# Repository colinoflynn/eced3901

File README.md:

ECED3901 - The Git REPO
-------------------------------
This GIT repo contains a lot of raw material from me teaching ECED3901 at Dalhousie University.
Be warned it's not designed to be used directly, but is provided as a service to those who might
need something from my teaching (source files, example code, etc.).

If you are taking the course, please consider the material on BBLearn (at dal.ca/bblearn) to be the
definitive resource. Things on this git repo are often *incomplete* or possibly even wrong for your
class.

Everything inside this repo can be assumed to be licensed CC-BY where possible (i.e. there is no more
restrictive license placed on it).

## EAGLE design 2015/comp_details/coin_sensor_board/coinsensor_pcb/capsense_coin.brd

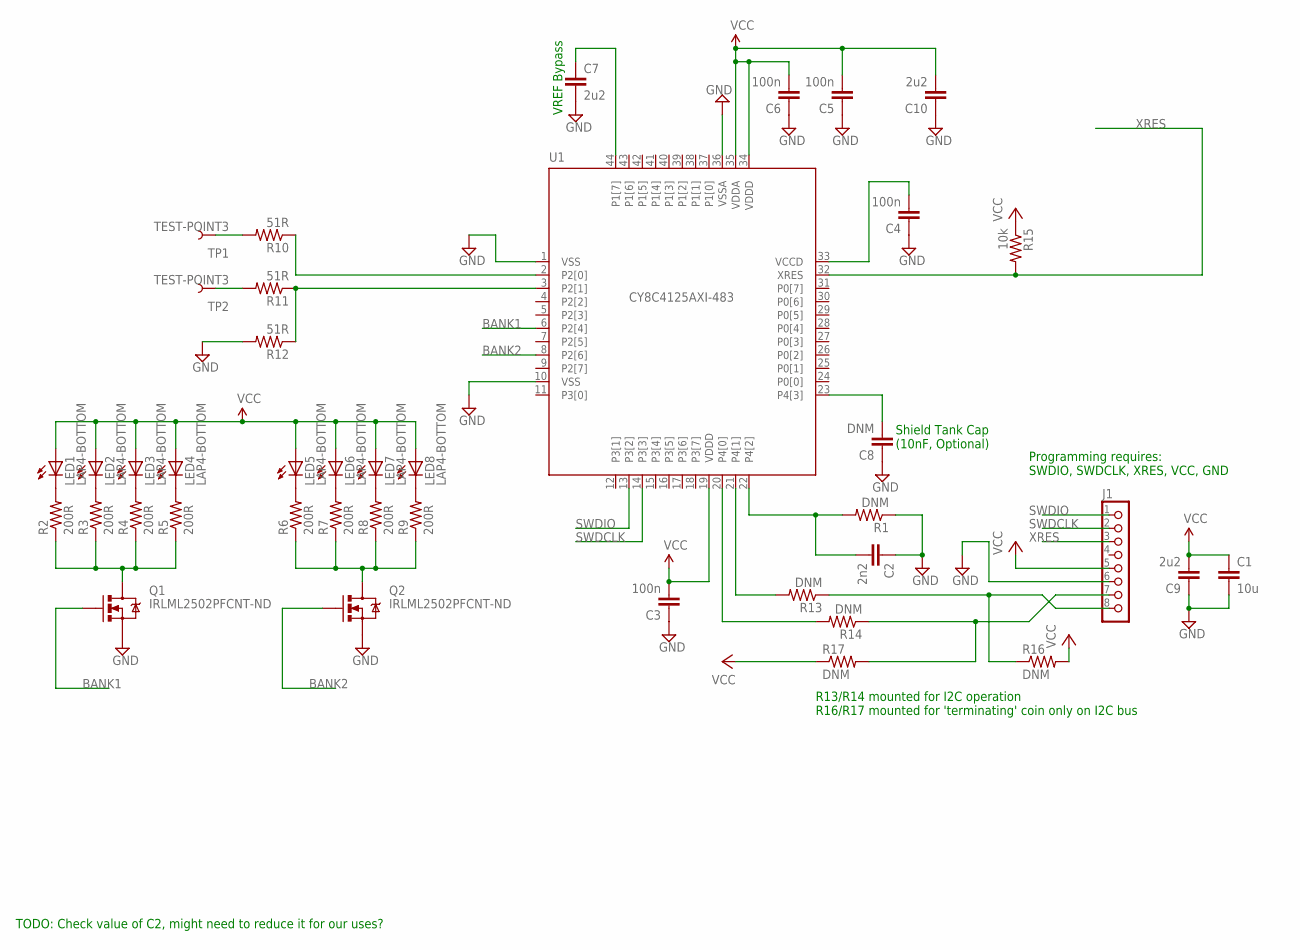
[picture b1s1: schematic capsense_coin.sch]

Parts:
C1: 10u; 0603C
C2: 2n2; 0603C
C3, C4, C5, C6: 100n; 0603C
C7, C9, C10: 2u2; 0603C
C8: DNM; 0603C
J1: CON_HEADER_1X08; DF13C-VERTSMD
LED1, LED2, LED3, LED4, LED5, LED6, LED7, LED8: LAP4-BOTTOM; P47F-BOTTOM
Q1, Q2: IRLML2502PFCNT-ND; SOT23
R1, R13, R14, R16, R17: DNM; 0603R
R2, R3, R4, R5, R6, R7, R8, R9: 200R; 0603R
R10, R11, R12: 51R; 0603R
R15: 10k; 0603R
TP1, TP2: TEST-POINT3; PAD.03X.03
U1: CY8C4125AXI-483; TQFP44

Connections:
BANK1: Q1.1 (G), U1.6 (P2[4])
BANK2: Q2.1 (G), U1.8 (P2[6])
GND: C1.2, C2.1, C3.1, C4.1, C5.1, C6.1, C7.2, C8.1, C9.1, C10.1, J1.6, Q1.2 (S), Q2.2 (S), R1.1, R12.2, U1.1 (VSS), U1.10 (VSS), U1.36 (VSSA)
unnamed: C2.2, R1.2, U1.22 (P4[2])
unnamed: C7.1, U1.44 (P1[7])
unnamed: C4.2, U1.33 (VCCD)
unnamed: C8.2, U1.23 (P4[3])
unnamed: LED1.C, R2.2
unnamed: LED2.C, R3.2
unnamed: LED3.C, R4.2
unnamed: LED4.C, R5.2
unnamed: LED5.C, R6.2
unnamed: LED6.C, R7.2
unnamed: LED7.C, R8.2
unnamed: LED8.C, R9.2
unnamed: Q1.3 (D), R2.1, R3.1, R4.1, R5.1
unnamed: Q2.3 (D), R6.1, R7.1, R8.1, R9.1
unnamed: R10.1, U1.2 (P2[0])
unnamed: R11.1, R12.1, U1.3 (P2[1])
unnamed: R13.2, U1.21 (P4[1])
unnamed: R14.2, U1.20 (P4[0])
unnamed: J1.8, R13.1, R16.1
unnamed: J1.7, R14.1, R17.2
P0[6]: U1.30 (P0[6])
P1[2]: U1.39 (P1[2])
P2[2]: U1.4 (P2[2])
P3[6]: U1.17 (P3[6])
SENSE: R10.2, TP1.P$1
SHIELD: R11.2, TP2.P$1
SWDCLK: J1.2, U1.14 (P3[3])
SWDIO: J1.1, U1.13 (P3[2])
VCC: C1.1, C3.2, C5.2, C6.2, C9.2, C10.2, J1.5, LED1.A, LED2.A, LED3.A, LED4.A, LED5.A, LED6.A, LED7.A, LED8.A, R15.1, R16.2, R17.1, U1.19 (VDDD), U1.34 (VDDD), U1.35 (VDDA)
XRES: J1.3, R15.2, U1.32 (XRES)

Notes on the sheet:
Shield Tank Cap (10nF, Optional)
VREF Bypass
R13/R14 mounted for I2C operation R16/R17 mounted for 'terminating' coin only on I2C bus
Programming requires: SWDIO, SWDCLK, XRES, VCC, GND
TODO: Check value of C2, might need to reduce it for our uses?

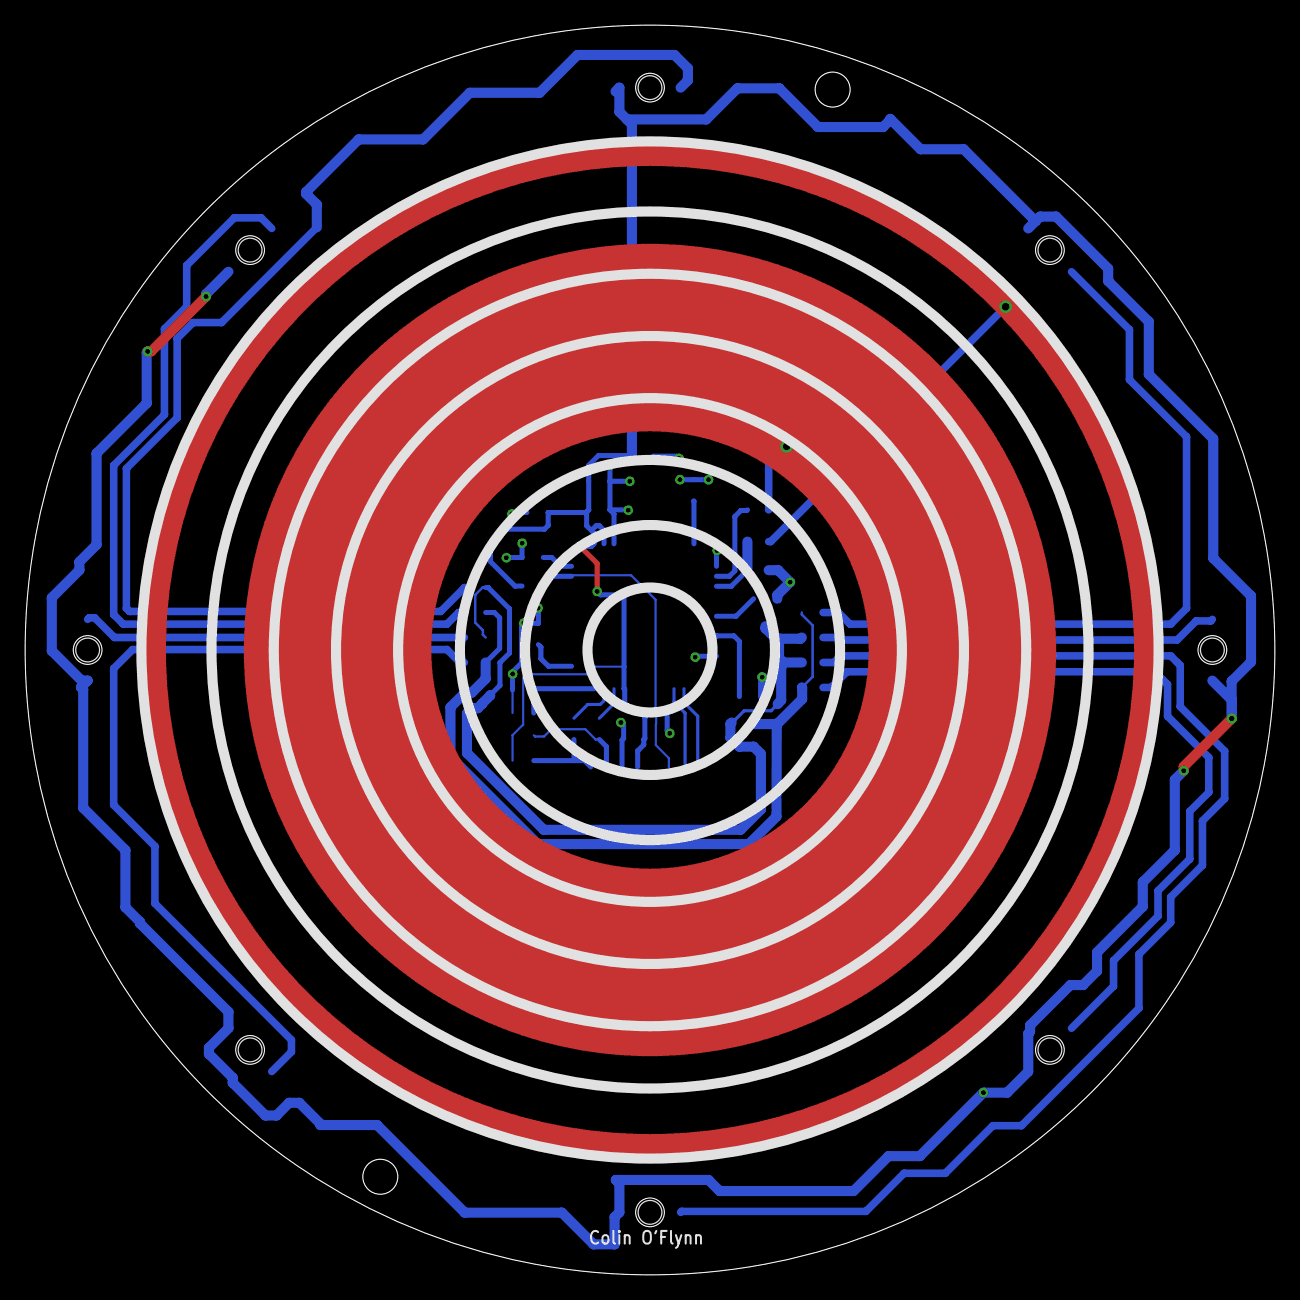
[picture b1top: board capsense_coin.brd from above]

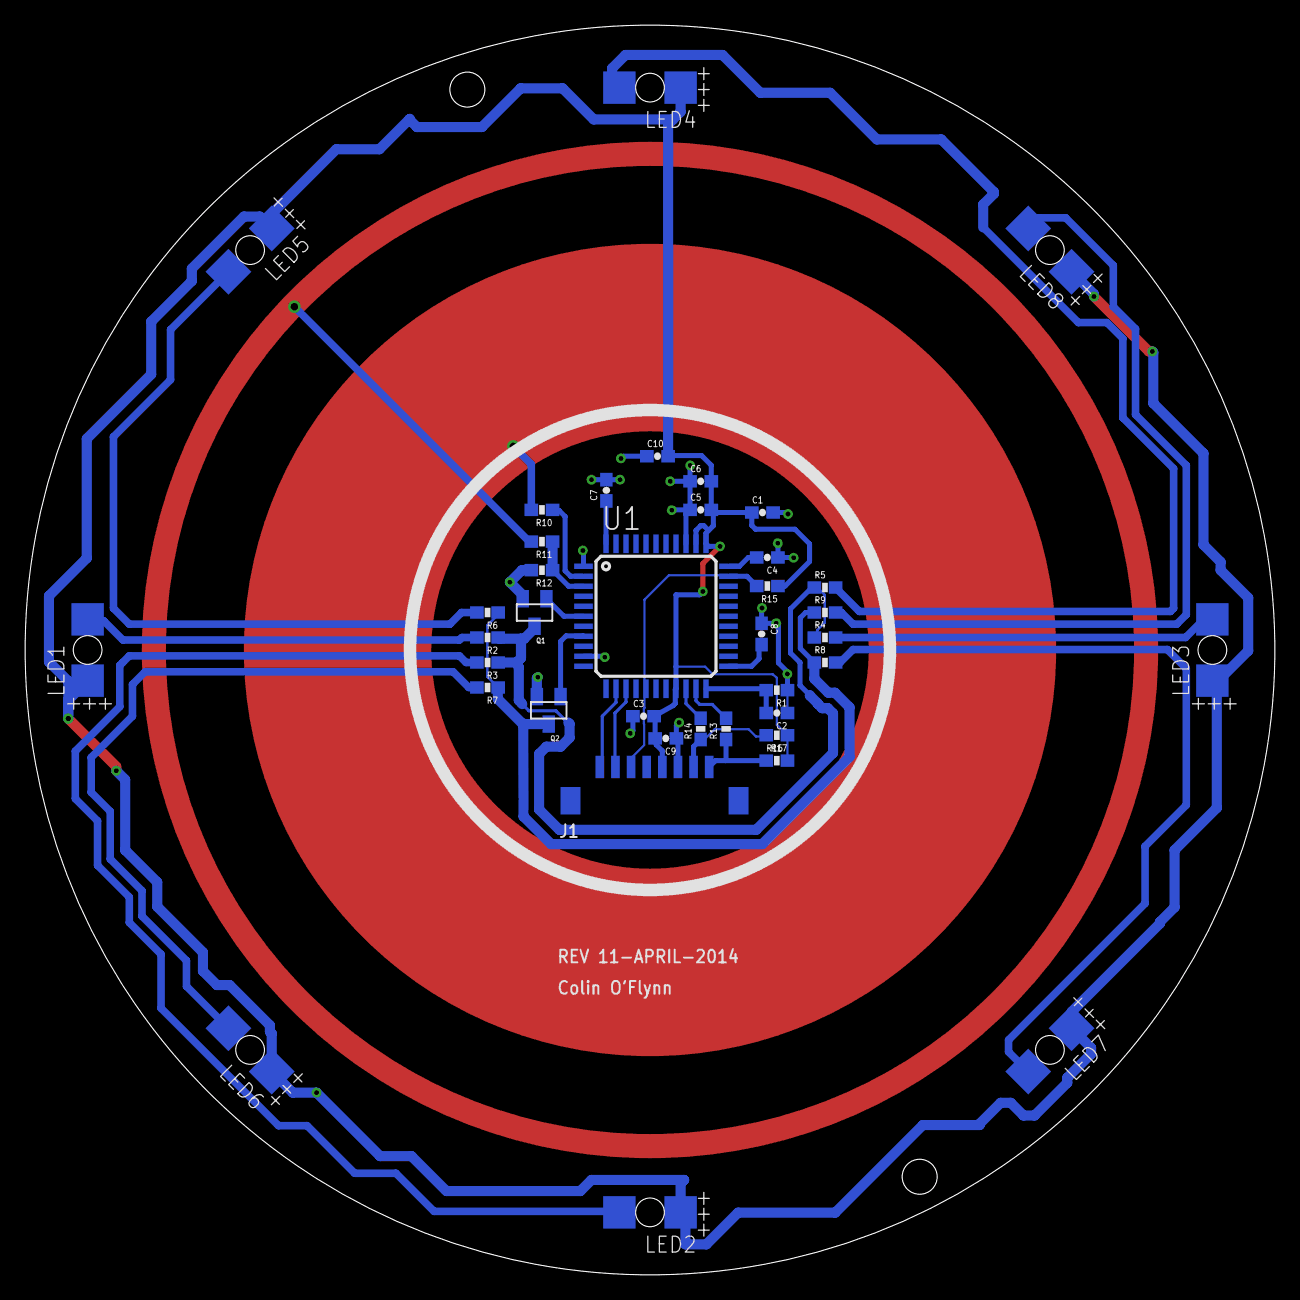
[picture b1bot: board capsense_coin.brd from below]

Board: 2 copper layers, 100.0 x 100.0 mm, 41 parts (39 on the bottom side), 29 nets.

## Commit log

2015-05-12 Add all the stuff
2015-05-12 Update capsense with values
2015-05-12 Add readme
2015-05-13 Update lecture 3
2015-05-14 Update PSOC project for coin board
2015-05-14 Update lecture #3
2015-06-14 Add more lectures
2015-06-14 Add lab #4 demo code

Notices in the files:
parts and their libraries:
SparkFun-DiscreteSemi: Licensing: Creative Commons ShareAlike 4.0 International - https://creativecommons.org/licenses/by-sa/4.0
SparkFun: Licensing: CC v3.0 Share-Alike You are welcome to use this library for commercial purposes.
